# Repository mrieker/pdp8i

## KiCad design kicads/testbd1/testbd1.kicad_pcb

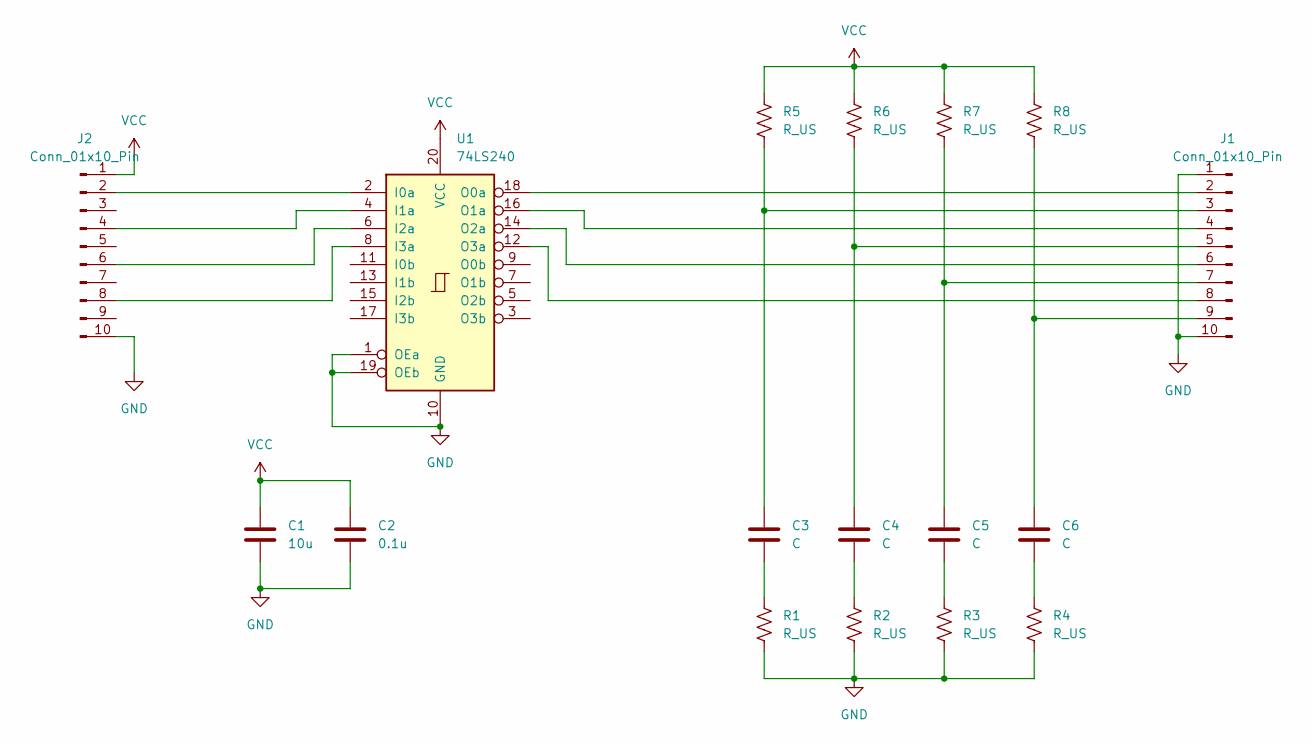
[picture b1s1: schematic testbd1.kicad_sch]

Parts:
C1: 10u; R_Axial_DIN0207_L6.3mm_D2.5mm_P10.16mm_Horizontal
C2: 0.1u; R_Axial_DIN0207_L6.3mm_D2.5mm_P10.16mm_Horizontal
C3, C4, C5, C6: C; R_Axial_DIN0207_L6.3mm_D2.5mm_P10.16mm_Horizontal
J1, J2: Conn_01x10_Pin; PinHeader_1x10_P2.54mm_Vertical
R1, R2, R3, R4, R5, R6, R7, R8: R_US; R_Axial_DIN0207_L6.3mm_D2.5mm_P10.16mm_Horizontal
U1: 74LS240; DIP-20_W7.62mm

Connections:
GND: C1.2, C2.2, J1.1, J1.10, J2.10, R1.2, R2.2, R3.2, R4.2, U1.1 (OEa), U1.10 (GND), U1.19 (OEb)
unnamed: C3.2, R1.1
unnamed: C4.2, R2.1
unnamed: C5.2, R3.1
unnamed: C6.2, R4.1
unnamed: J1.2, U1.18 (O0a)
unnamed: C3.1, J1.3, R5.2
unnamed: J1.4, U1.16 (O1a)
unnamed: C4.1, J1.5, R6.2
unnamed: J1.6, U1.14 (O2a)
unnamed: C5.1, J1.7, R7.2
unnamed: J1.8, U1.12 (O3a)
unnamed: C6.1, J1.9, R8.2
unnamed: J2.2, U1.2 (I0a)
unnamed: J2.4, U1.4 (I1a)
unnamed: J2.6, U1.6 (I2a)
unnamed: J2.8, U1.8 (I3a)
VCC: C1.1, C2.1, J2.1, R5.1, R6.1, R7.1, R8.1, U1.20 (VCC)

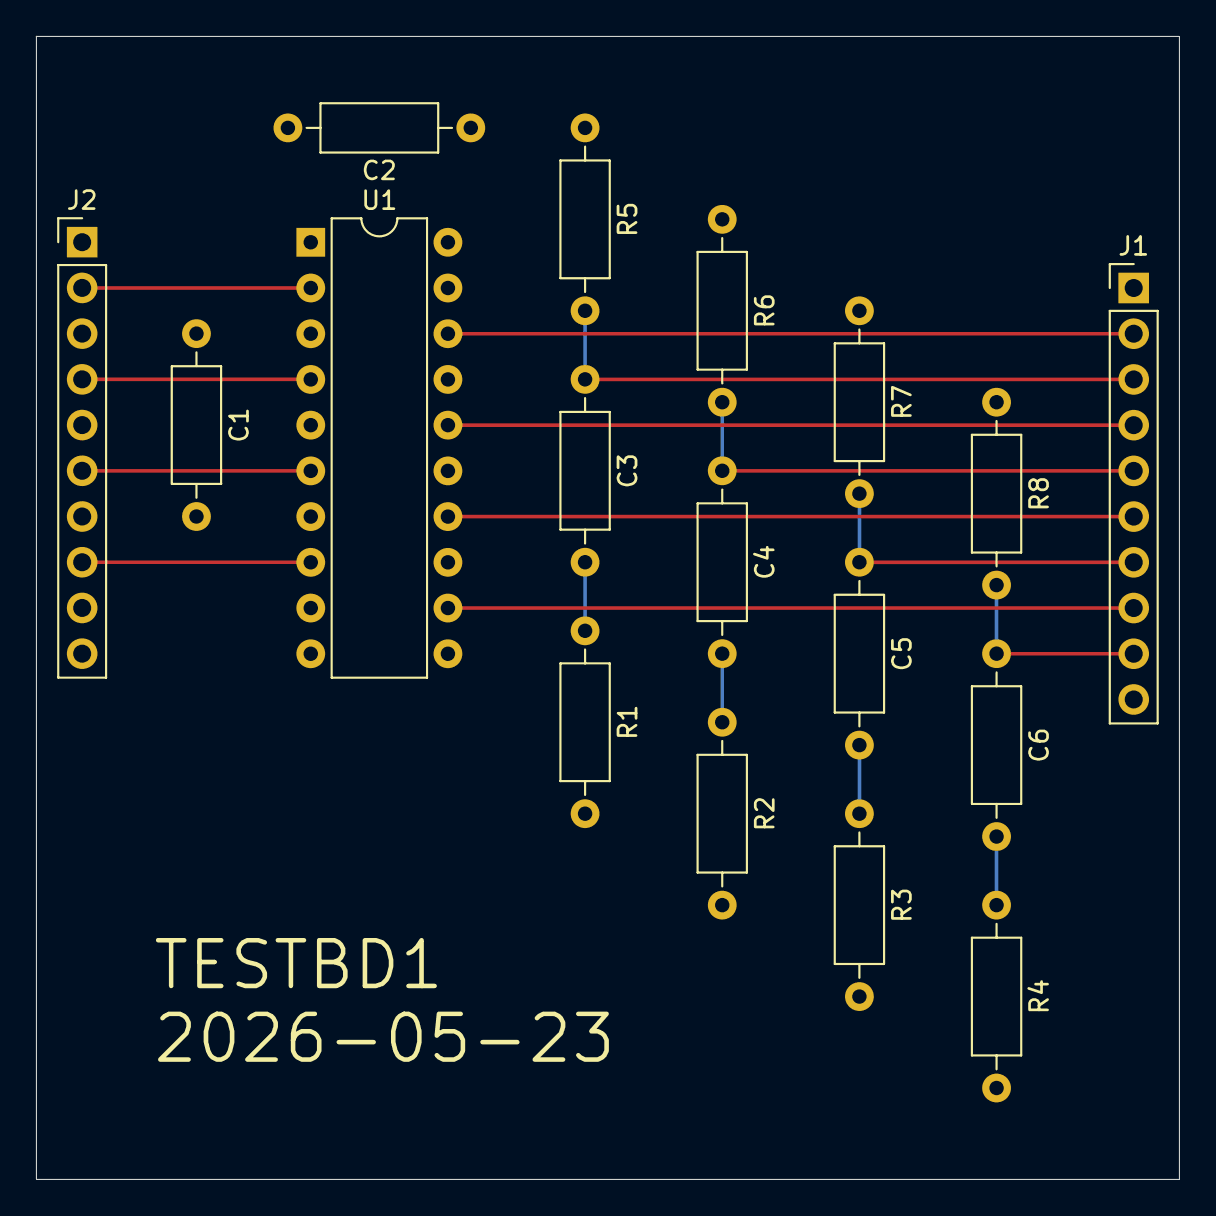
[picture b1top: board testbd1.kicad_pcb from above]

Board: 4 copper layers, 63.5 x 63.5 mm, 17 parts (0 on the bottom side), 18 nets.

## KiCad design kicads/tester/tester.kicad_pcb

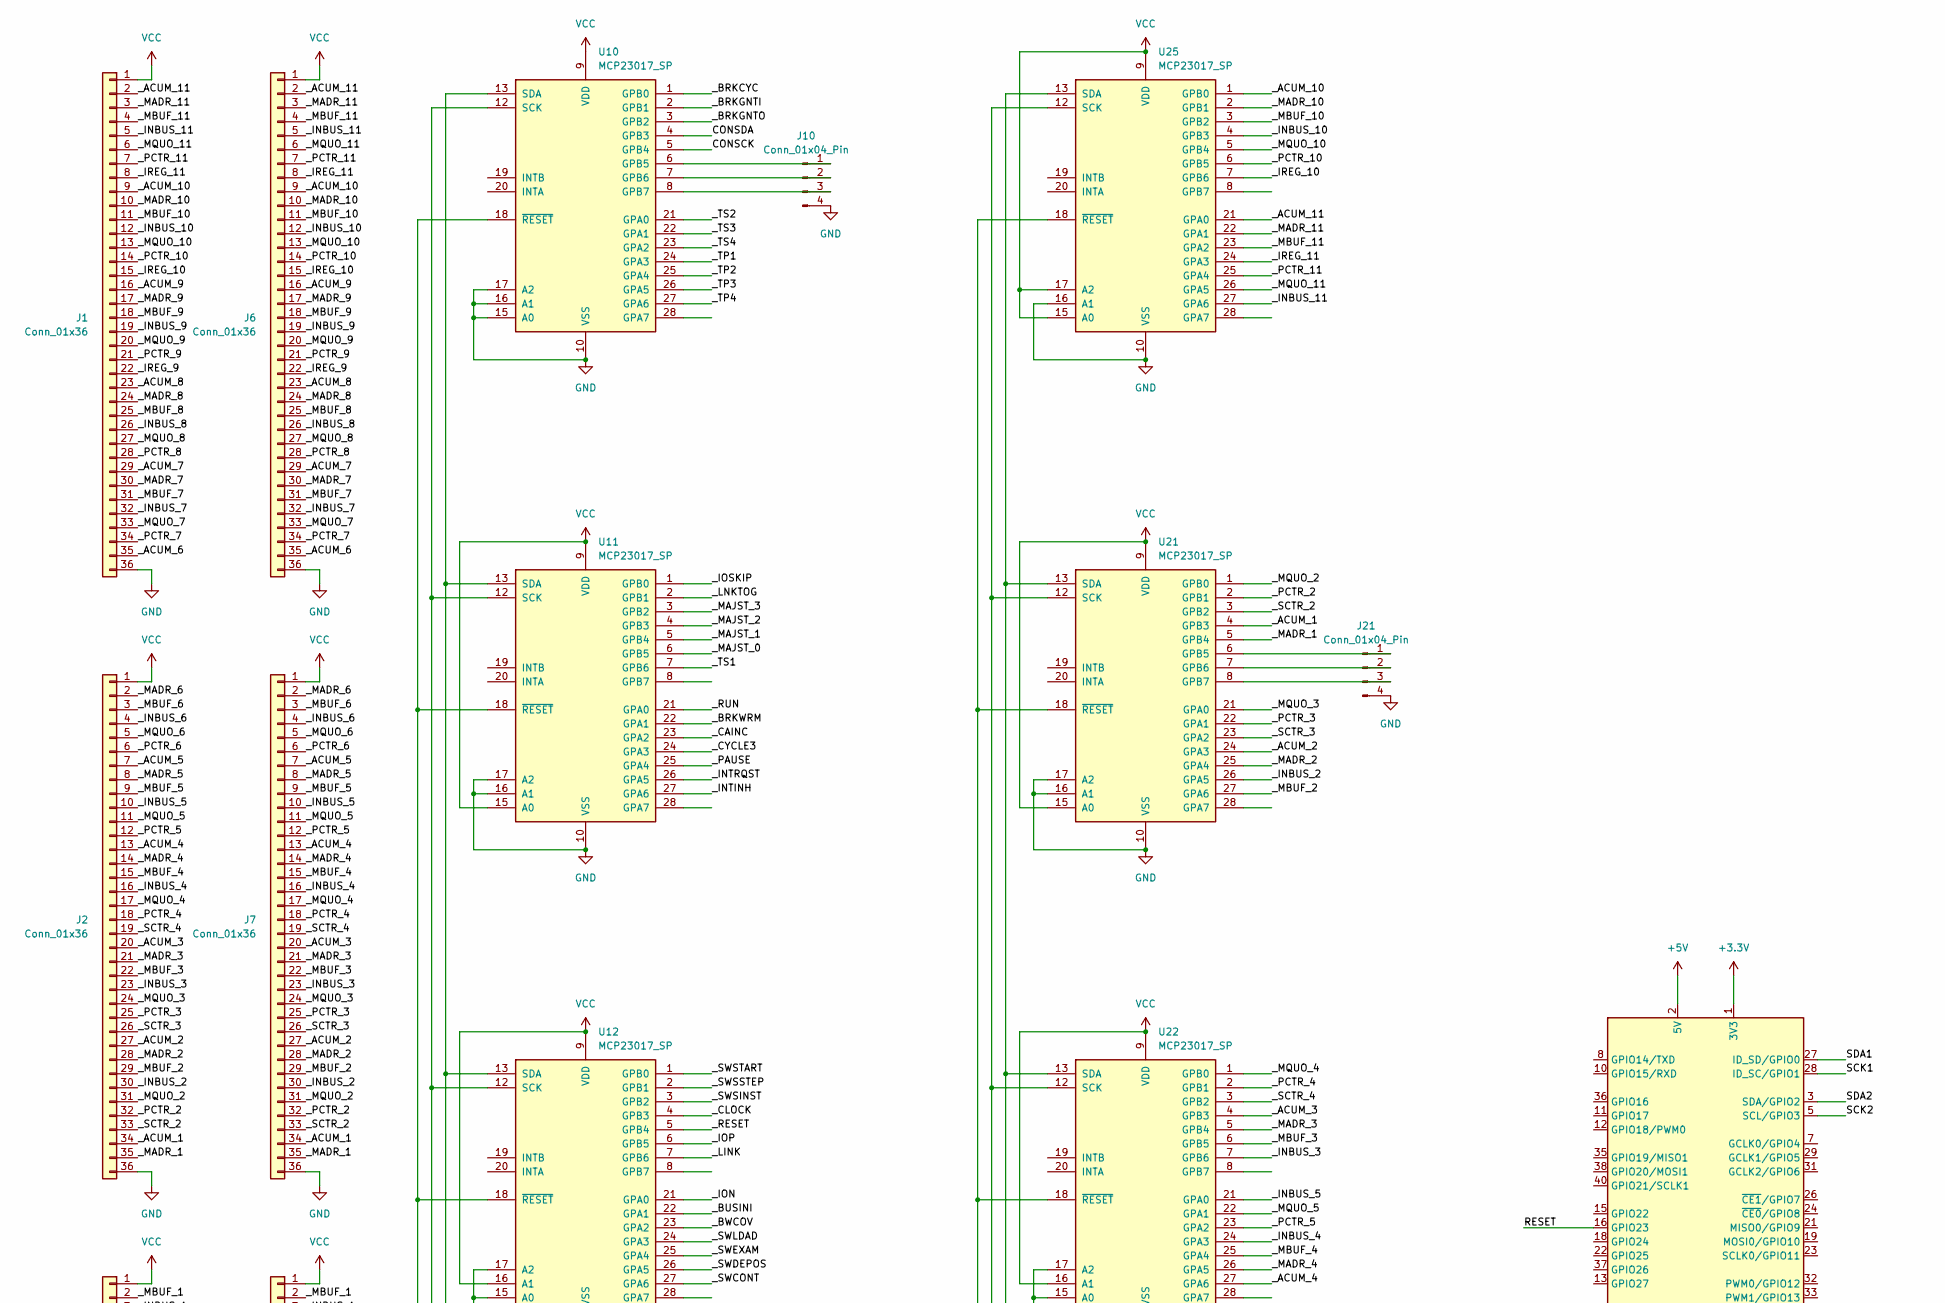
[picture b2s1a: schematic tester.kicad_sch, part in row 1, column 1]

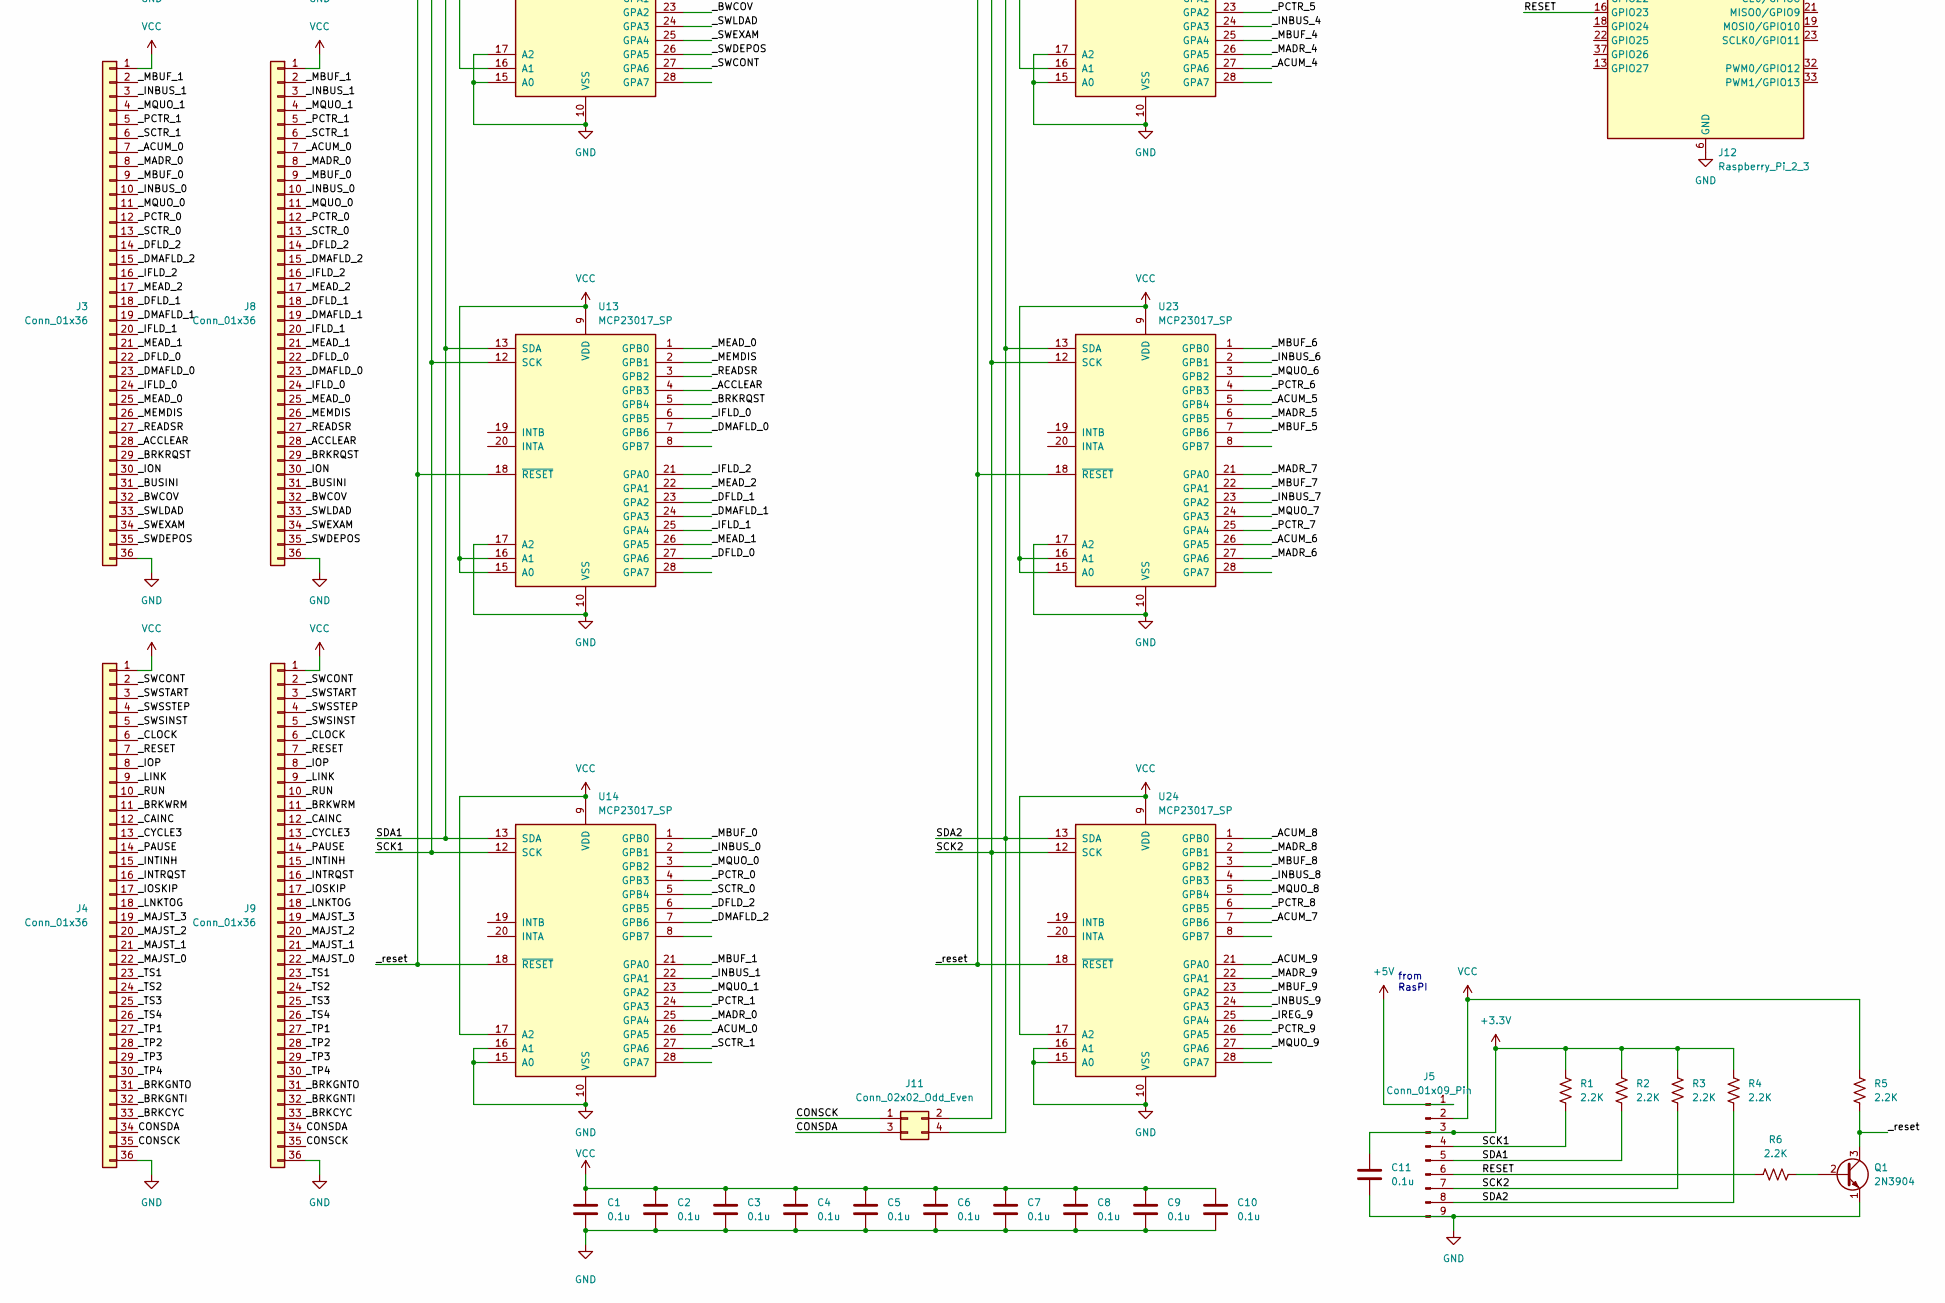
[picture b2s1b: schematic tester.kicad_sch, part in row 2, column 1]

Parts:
C1, C2, C3, C4, C5, C6, C7, C8, C9, C10, C11: 0.1u; R_Axial_DIN0207_L6.3mm_D2.5mm_P7.62mm_Horizontal
J1, J2, J3, J4, J6, J7, J8, J9: Conn_01x36; PinHeader_1x36_P2.54mm_Vertical
J5: Conn_01x09_Pin; PinHeader_1x09_P2.54mm_Vertical
J10, J21: Conn_01x04_Pin; PinHeader_1x04_P2.54mm_Vertical
J11: Conn_02x02_Odd_Even; PinHeader_2x02_P2.54mm_Vertical
J12: Raspberry_Pi_2_3; PinHeader_2x20_P2.54mm_Vertical
Q1: 2N3904; TO-92_Wide
R1, R2, R3, R4, R5, R6: 2.2K; R_Axial_DIN0204_L3.6mm_D1.6mm_P7.62mm_Horizontal
U10, U11, U12, U13, U14, U21, U22, U23, U24, U25: MCP23017_SP; DIP-28_W7.62mm

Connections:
+3.3V: C11.1, J5.3, J12.1 (3V3), J12.17 (3V3), R1.1, R2.1, R3.1, R4.1
+5V: J5.1, J12.2 (5V), J12.4 (5V)
/CONSCK: J4.35, J9.35, J11.1, U10.5 (GPB4)
/CONSDA: J4.34, J9.34, J11.3, U10.4 (GPB3)
/RESET: J5.6, J12.16 (GPIO23), R6.1
/SCK1: J5.4, J12.28 (ID_SC/GPIO1), R1.2, U10.12 (SCK), U11.12 (SCK), U12.12 (SCK), U13.12 (SCK), U14.12 (SCK)
/SCK2: J5.7, J11.2, J12.5 (SCL/GPIO3), R3.2, U21.12 (SCK), U22.12 (SCK), U23.12 (SCK), U24.12 (SCK), U25.12 (SCK)
/SDA1: J5.5, J12.27 (ID_SD/GPIO0), R2.2, U10.13 (SDA), U11.13 (SDA), U12.13 (SDA), U13.13 (SDA), U14.13 (SDA)
/SDA2: J5.8, J11.4, J12.3 (SDA/GPIO2), R4.2, U21.13 (SDA), U22.13 (SDA), U23.13 (SDA), U24.13 (SDA), U25.13 (SDA)
/_ACCLEAR: J3.28, J8.28, U13.4 (GPB3)
/_ACUM_0: J3.7, J8.7, U14.26 (GPA5)
/_ACUM_1: J2.34, J7.34, U21.4 (GPB3)
/_ACUM_2: J2.27, J7.27, U21.24 (GPA3)
/_ACUM_3: J2.20, J7.20, U22.4 (GPB3)
/_ACUM_4: J2.13, J7.13, U22.27 (GPA6)
/_ACUM_5: J2.7, J7.7, U23.5 (GPB4)
/_ACUM_6: J1.35, J6.35, U23.26 (GPA5)
/_ACUM_7: J1.29, J6.29, U24.7 (GPB6)
/_ACUM_8: J1.23, J6.23, U24.1 (GPB0)
/_ACUM_9: J1.16, J6.16, U24.21 (GPA0)
/_ACUM_10: J1.9, J6.9, U25.1 (GPB0)
/_ACUM_11: J1.2, J6.2, U25.21 (GPA0)
/_BRKCYC: J4.33, J9.33, U10.1 (GPB0)
/_BRKGNTI: J4.32, J9.32, U10.2 (GPB1)
/_BRKGNTO: J4.31, J9.31, U10.3 (GPB2)
/_BRKRQST: J3.29, J8.29, U13.5 (GPB4)
/_BRKWRM: J4.11, J9.11, U11.22 (GPA1)
/_BUSINI: J3.31, J8.31, U12.22 (GPA1)
/_BWCOV: J3.32, J8.32, U12.23 (GPA2)
/_CAINC: J4.12, J9.12, U11.23 (GPA2)
/_CLOCK: J4.6, J9.6, U12.4 (GPB3)
/_CYCLE3: J4.13, J9.13, U11.24 (GPA3)
/_DFLD_0: J3.22, J8.22, U13.27 (GPA6)
/_DFLD_1: J3.18, J8.18, U13.23 (GPA2)
/_DFLD_2: J3.14, J8.14, U14.6 (GPB5)
/_DMAFLD_0: J3.23, J8.23, U13.7 (GPB6)
/_DMAFLD_1: J3.19, J8.19, U13.24 (GPA3)
/_DMAFLD_2: J3.15, J8.15, U14.7 (GPB6)
/_IFLD_0: J3.24, J8.24, U13.6 (GPB5)
/_IFLD_1: J3.20, J8.20, U13.25 (GPA4)
/_IFLD_2: J3.16, J8.16, U13.21 (GPA0)
/_INBUS_0: J3.10, J8.10, U14.2 (GPB1)
/_INBUS_1: J3.3, J8.3, U14.22 (GPA1)
/_INBUS_2: J2.30, J7.30, U21.26 (GPA5)
/_INBUS_3: J2.23, J7.23, U22.7 (GPB6)
/_INBUS_4: J2.16, J7.16, U22.24 (GPA3)
/_INBUS_5: J2.10, J7.10, U22.21 (GPA0)
/_INBUS_6: J2.4, J7.4, U23.2 (GPB1)
/_INBUS_7: J1.32, J6.32, U23.23 (GPA2)
/_INBUS_8: J1.26, J6.26, U24.4 (GPB3)
/_INBUS_9: J1.19, J6.19, U24.24 (GPA3)
/_INBUS_10: J1.12, J6.12, U25.4 (GPB3)
/_INBUS_11: J1.5, J6.5, U25.27 (GPA6)
/_INTINH: J4.15, J9.15, U11.27 (GPA6)
/_INTRQST: J4.16, J9.16, U11.26 (GPA5)
/_ION: J3.30, J8.30, U12.21 (GPA0)
/_IOP: J4.8, J9.8, U12.6 (GPB5)
/_IOSKIP: J4.17, J9.17, U11.1 (GPB0)
/_IREG_9: J1.22, J6.22, U24.25 (GPA4)
/_IREG_10: J1.15, J6.15, U25.7 (GPB6)
/_IREG_11: J1.8, J6.8, U25.24 (GPA3)
/_LINK: J4.9, J9.9, U12.7 (GPB6)
/_LNKTOG: J4.18, J9.18, U11.2 (GPB1)
/_MADR_0: J3.8, J8.8, U14.25 (GPA4)
/_MADR_1: J2.35, J7.35, U21.5 (GPB4)
/_MADR_2: J2.28, J7.28, U21.25 (GPA4)
/_MADR_3: J2.21, J7.21, U22.5 (GPB4)
/_MADR_4: J2.14, J7.14, U22.26 (GPA5)
/_MADR_5: J2.8, J7.8, U23.6 (GPB5)
/_MADR_6: J2.2, J7.2, U23.27 (GPA6)
/_MADR_7: J1.30, J6.30, U23.21 (GPA0)
/_MADR_8: J1.24, J6.24, U24.2 (GPB1)
/_MADR_9: J1.17, J6.17, U24.22 (GPA1)
/_MADR_10: J1.10, J6.10, U25.2 (GPB1)
/_MADR_11: J1.3, J6.3, U25.22 (GPA1)
/_MAJST_0: J4.22, J9.22, U11.6 (GPB5)
/_MAJST_1: J4.21, J9.21, U11.5 (GPB4)
/_MAJST_2: J4.20, J9.20, U11.4 (GPB3)
/_MAJST_3: J4.19, J9.19, U11.3 (GPB2)
/_MBUF_0: J3.9, J8.9, U14.1 (GPB0)
/_MBUF_1: J3.2, J8.2, U14.21 (GPA0)
/_MBUF_2: J2.29, J7.29, U21.27 (GPA6)
/_MBUF_3: J2.22, J7.22, U22.6 (GPB5)
/_MBUF_4: J2.15, J7.15, U22.25 (GPA4)
/_MBUF_5: J2.9, J7.9, U23.7 (GPB6)
/_MBUF_6: J2.3, J7.3, U23.1 (GPB0)
/_MBUF_7: J1.31, J6.31, U23.22 (GPA1)
/_MBUF_8: J1.25, J6.25, U24.3 (GPB2)
/_MBUF_9: J1.18, J6.18, U24.23 (GPA2)
/_MBUF_10: J1.11, J6.11, U25.3 (GPB2)
/_MBUF_11: J1.4, J6.4, U25.23 (GPA2)
/_MEAD_0: J3.25, J8.25, U13.1 (GPB0)
/_MEAD_1: J3.21, J8.21, U13.26 (GPA5)
/_MEAD_2: J3.17, J8.17, U13.22 (GPA1)
/_MEMDIS: J3.26, J8.26, U13.2 (GPB1)
/_MQUO_0: J3.11, J8.11, U14.3 (GPB2)
/_MQUO_1: J3.4, J8.4, U14.23 (GPA2)
/_MQUO_2: J2.31, J7.31, U21.1 (GPB0)
/_MQUO_3: J2.24, J7.24, U21.21 (GPA0)
/_MQUO_4: J2.17, J7.17, U22.1 (GPB0)
/_MQUO_5: J2.11, J7.11, U22.22 (GPA1)
/_MQUO_6: J2.5, J7.5, U23.3 (GPB2)
/_MQUO_7: J1.33, J6.33, U23.24 (GPA3)
/_MQUO_8: J1.27, J6.27, U24.5 (GPB4)
/_MQUO_9: J1.20, J6.20, U24.27 (GPA6)
/_MQUO_10: J1.13, J6.13, U25.5 (GPB4)
/_MQUO_11: J1.6, J6.6, U25.26 (GPA5)
/_PAUSE: J4.14, J9.14, U11.25 (GPA4)
/_PCTR_0: J3.12, J8.12, U14.4 (GPB3)
/_PCTR_1: J3.5, J8.5, U14.24 (GPA3)
/_PCTR_2: J2.32, J7.32, U21.2 (GPB1)
/_PCTR_3: J2.25, J7.25, U21.22 (GPA1)
/_PCTR_4: J2.18, J7.18, U22.2 (GPB1)
/_PCTR_5: J2.12, J7.12, U22.23 (GPA2)
/_PCTR_6: J2.6, J7.6, U23.4 (GPB3)
/_PCTR_7: J1.34, J6.34, U23.25 (GPA4)
/_PCTR_8: J1.28, J6.28, U24.6 (GPB5)
/_PCTR_9: J1.21, J6.21, U24.26 (GPA5)
/_PCTR_10: J1.14, J6.14, U25.6 (GPB5)
/_PCTR_11: J1.7, J6.7, U25.25 (GPA4)
/_READSR: J3.27, J8.27, U13.3 (GPB2)
/_RESET: J4.7, J9.7, U12.5 (GPB4)
/_RUN: J4.10, J9.10, U11.21 (GPA0)
/_SCTR_0: J3.13, J8.13, U14.5 (GPB4)
/_SCTR_1: J3.6, J8.6, U14.27 (GPA6)
/_SCTR_2: J2.33, J7.33, U21.3 (GPB2)
/_SCTR_3: J2.26, J7.26, U21.23 (GPA2)
/_SCTR_4: J2.19, J7.19, U22.3 (GPB2)
/_SWCONT: J4.2, J9.2, U12.27 (GPA6)
/_SWDEPOS: J3.35, J8.35, U12.26 (GPA5)
/_SWEXAM: J3.34, J8.34, U12.25 (GPA4)
/_SWLDAD: J3.33, J8.33, U12.24 (GPA3)
/_SWSINST: J4.5, J9.5, U12.3 (GPB2)
/_SWSSTEP: J4.4, J9.4, U12.2 (GPB1)
/_SWSTART: J4.3, J9.3, U12.1 (GPB0)
/_TP1: J4.27, J9.27, U10.24 (GPA3)
/_TP2: J4.28, J9.28, U10.25 (GPA4)
/_TP3: J4.29, J9.29, U10.26 (GPA5)
/_TP4: J4.30, J9.30, U10.27 (GPA6)
/_TS1: J4.23, J9.23, U11.7 (GPB6)
/_TS2: J4.24, J9.24, U10.21 (GPA0)
/_TS3: J4.25, J9.25, U10.22 (GPA1)
/_TS4: J4.26, J9.26, U10.23 (GPA2)
/_reset: Q1.3 (C), R5.2, U10.18 (~RESET), U11.18 (~RESET), U12.18 (~RESET), U13.18 (~RESET), U14.18 (~RESET), U21.18 (~RESET), U22.18 (~RESET), U23.18 (~RESET), U24.18 (~RESET), U25.18 (~RESET)
GND: C1.2, C2.2, C3.2, C4.2, C5.2, C6.2, C7.2, C8.2, C9.2, C10.2, C11.2, J1.36, J2.36, J3.36, J4.36, J5.9, J6.36, J7.36, J8.36, J9.36, J10.4, J12.6 (GND), J12.9 (GND), J12.14 (GND), J12.20 (GND), J12.25 (GND), J12.30 (GND), J12.34 (GND), J12.39 (GND), J21.4, Q1.1 (E), U10.10 (VSS), U10.15 (A0), U10.16 (A1), U10.17 (A2), U11.10 (VSS), U11.16 (A1), U11.17 (A2), U12.10 (VSS), U12.15 (A0), U12.17 (A2), U13.10 (VSS), U13.17 (A2), U14.10 (VSS), U14.15 (A0), U14.16 (A1), U21.10 (VSS), U21.16 (A1), U21.17 (A2), U22.10 (VSS), U22.15 (A0), U22.17 (A2), U23.10 (VSS), U23.17 (A2), U24.10 (VSS), U24.15 (A0), U24.16 (A1), U25.10 (VSS), U25.16 (A1)
unnamed: J10.1, U10.6 (GPB5)
unnamed: J10.2, U10.7 (GPB6)
unnamed: J10.3, U10.8 (GPB7)
unnamed: J21.1, U21.6 (GPB5)
unnamed: J21.2, U21.7 (GPB6)
unnamed: J21.3, U21.8 (GPB7)
unnamed: Q1.2 (B), R6.2
VCC: C1.1, C2.1, C3.1, C4.1, C5.1, C6.1, C7.1, C8.1, C9.1, C10.1, J1.1, J2.1, J3.1, J4.1, J5.2, J6.1, J7.1, J8.1, J9.1, R5.1, U10.9 (VDD), U11.9 (VDD), U11.15 (A0), U12.9 (VDD), U12.16 (A1), U13.9 (VDD), U13.15 (A0), U13.16 (A1), U14.9 (VDD), U14.17 (A2), U21.9 (VDD), U21.15 (A0), U22.9 (VDD), U22.16 (A1), U23.9 (VDD), U23.15 (A0), U23.16 (A1), U24.9 (VDD), U24.17 (A2), U25.9 (VDD), U25.15 (A0), U25.17 (A2)

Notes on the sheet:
from RasPI

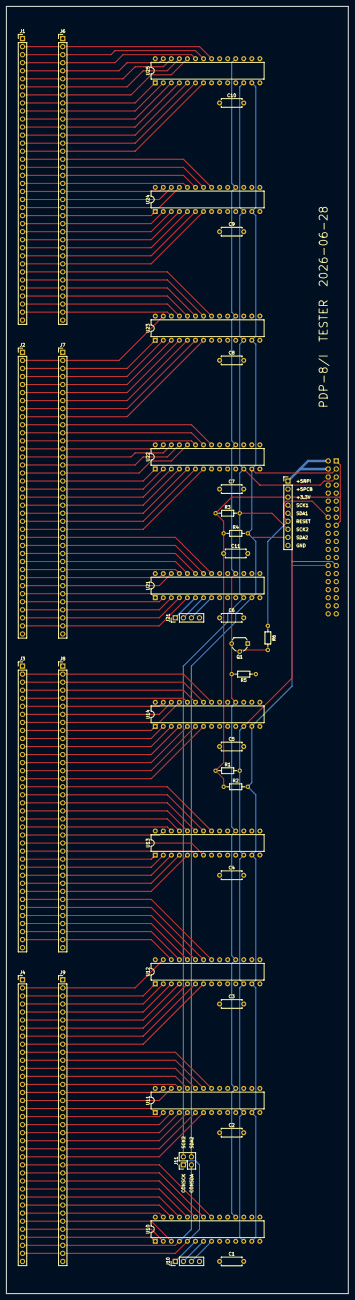
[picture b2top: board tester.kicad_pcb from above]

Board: 4 copper layers, 108.0 x 406.4 mm, 41 parts (1 on the bottom side), 153 nets.
